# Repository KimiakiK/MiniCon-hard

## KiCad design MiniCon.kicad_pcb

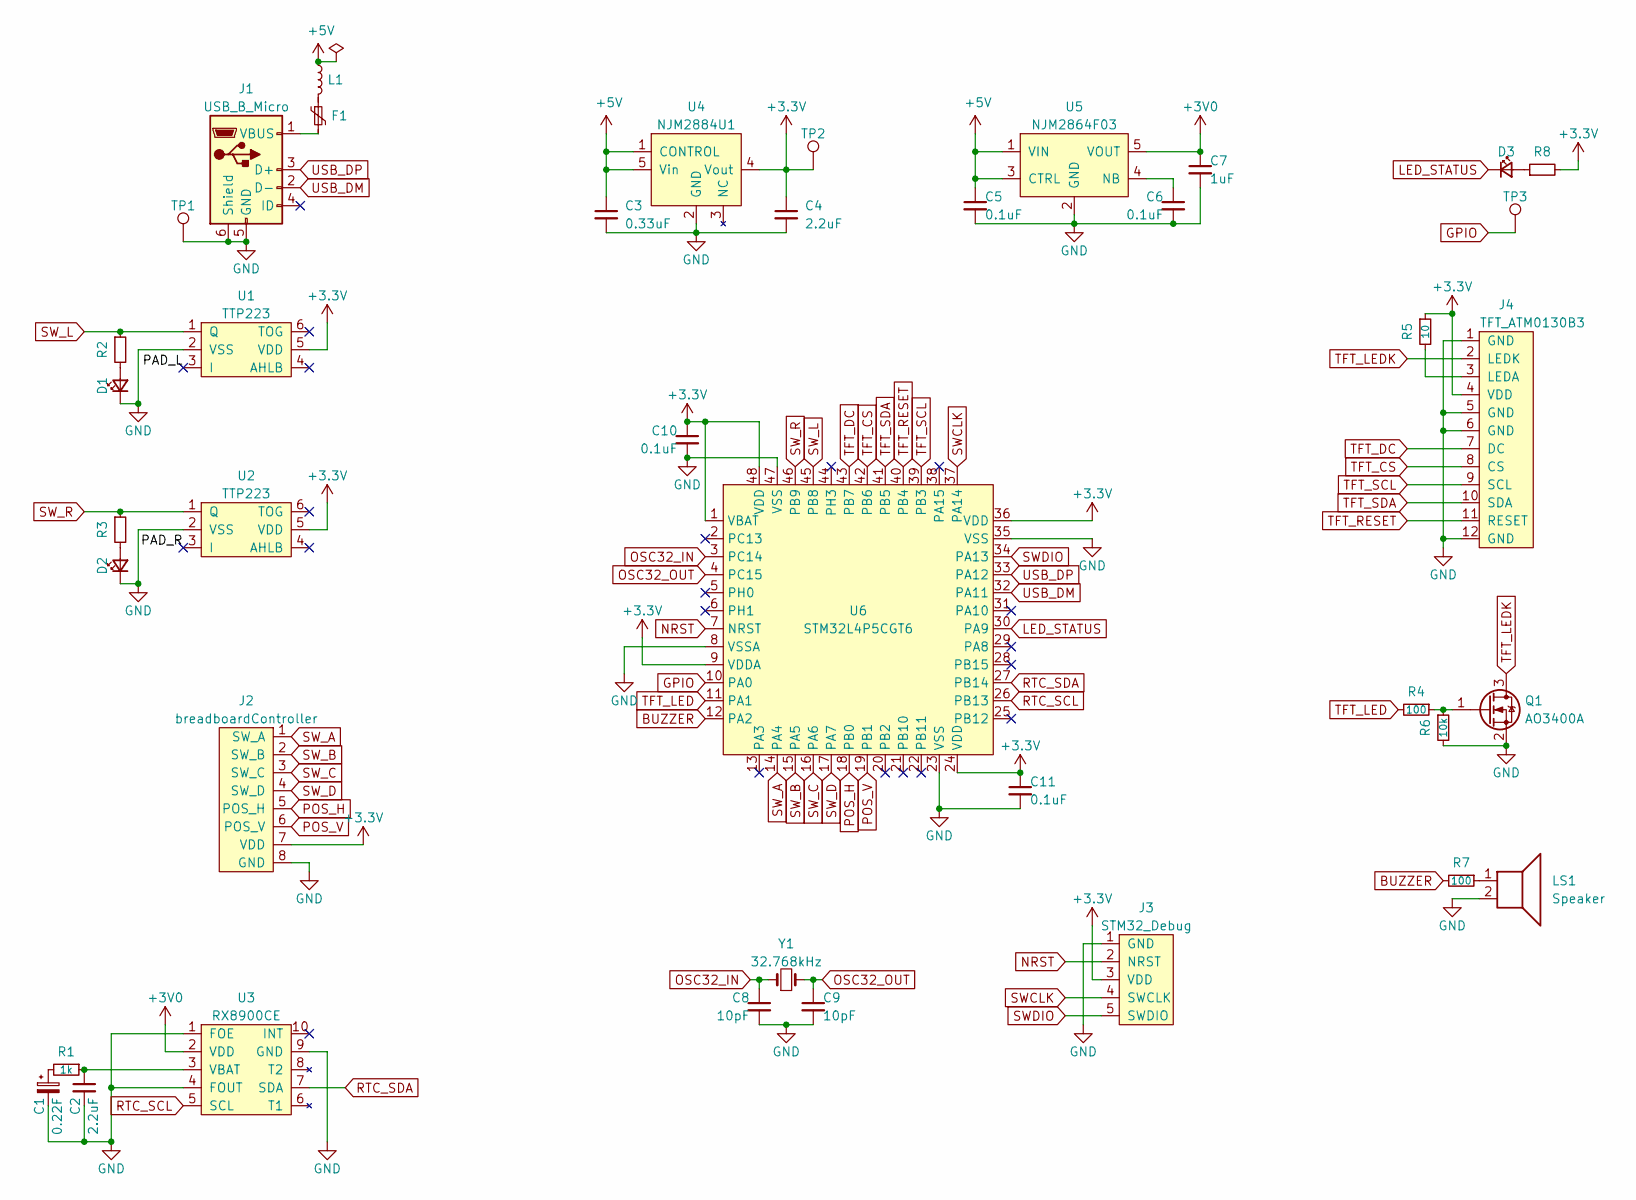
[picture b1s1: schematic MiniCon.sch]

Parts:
C1: 0.22F; DCK-3R3E224-E
C2, C4: 2.2uF; 1608Metric
C3: 0.33uF; 1608Metric
C5, C6, C10, C11: 0.1uF; 1608Metric
C7: 1uF; 1608Metric
C8, C9: 10pF; 1005Metric
D1, D2, D3: LED; 1608Metric
F1: Polyfuse; 1608Metric
J1: USB_B_Micro; ZX62-B-5PA
J2: breadboardController; PinHeader_1x08_P2.54mm_Vertical
J3: STM32_Debug; STM32_Debug_5pin
J4: TFT_ATM0130B3; Hirose_FH12-12S-0.5SH_1x12-1MP_P0.50mm_Horizontal
L1: L; 1608Metric
LS1: Speaker; PKMCS0909E4000
Q1: AO3400A; SOT-23
R1: 1k; 1608Metric
R2, R3, R8: R; 1608Metric
R4, R7: 100; 1608Metric
R5: 10; 1608Metric
R6: 10k; 1608Metric
TP1, TP2, TP3: TestPoint; TestPoint_THTPad_D1.3mm_Drill0.8mm
U1, U2: TTP223; SOT-23-6
U3: RX8900CE
U4: NJM2884U1; SOT-89-5
U5: NJM2864F03; SOT-23-5
U6: STM32L4P5CGT6; LQFP-48_7x7mm_P0.5mm_FusionPCB
Y1: 32.768kHz; Crystal_SMD_3215-2Pin

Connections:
+3V0: C7.1, U3.2 (VDD), U5.5 (VOUT)
+3V3: C4.1, C10.1, C11.1, J2.7 (VDD), J3.3 (VDD), J4.4 (VDD), R5.1, R8.2, TP2.1, U1.5 (VDD), U2.5 (VDD), U4.4 (Vout), U6.1 (VBAT), U6.9 (VDDA), U6.24 (VDD), U6.36 (VDD), U6.48 (VDD)
+5V: C3.1, C5.1, L1.1, U4.1 (CONTROL), U4.5 (Vin), U5.1 (VIN), U5.3 (CTRL)
/PAD_L: U1.3 (I)
/PAD_R: U2.3 (I)
BUZZER: R7.2, U6.12 (PA2)
GND: C1.2, C2.2, C3.2, C4.2, C5.2, C6.2, C7.2, C8.2, C9.2, C10.2, C11.2, D1.1 (K), D2.1 (K), J1.5 (GND), J1.6 (Shield), J2.8 (GND), J3.1 (GND), J4.1 (GND), J4.5 (GND), J4.6 (GND), J4.12 (GND), LS1.2, Q1.2 (S), R6.2, TP1.1, U1.2 (VSS), U2.2 (VSS), U3.1 (FOE), U3.4 (FOUT), U3.9 (GND), U4.2 (GND), U5.2 (GND), U6.8 (VSSA), U6.23 (VSS), U6.35 (VSS), U6.47 (VSS)
GPIO: TP3.1, U6.10 (PA0)
LED_STATUS: D3.1 (K), U6.30 (PA9)
NRST: J3.2 (NRST), U6.7 (NRST)
unnamed: C1.1, R1.2
unnamed: C2.1, R1.1, U3.3 (VBAT)
unnamed: C6.1, U5.4 (NB)
unnamed: D1.2 (A), R2.2
unnamed: D2.2 (A), R3.2
unnamed: D3.2 (A), R8.1
unnamed: F1.1, L1.2
unnamed: F1.2, J1.1 (VBUS)
unnamed: J4.3 (LEDA), R5.2
unnamed: LS1.1, R7.1
unnamed: Q1.1 (G), R4.1, R6.1
OSC32_IN: C8.1, U6.3 (PC14), Y1.1
OSC32_OUT: C9.1, U6.4 (PC15), Y1.2
POS_H: J2.5 (POS_H), U6.18 (PB0)
POS_V: J2.6 (POS_V), U6.19 (PB1)
RTC_SCL: U3.5 (SCL), U6.26 (PB13)
RTC_SDA: U3.7 (SDA), U6.27 (PB14)
SWCLK: J3.4 (SWCLK), U6.37 (PA14)
SWDIO: J3.5 (SWDIO), U6.34 (PA13)
SW_A: J2.1 (SW_A), U6.14 (PA4)
SW_B: J2.2 (SW_B), U6.15 (PA5)
SW_C: J2.3 (SW_C), U6.16 (PA6)
SW_D: J2.4 (SW_D), U6.17 (PA7)
SW_L: R2.1, U1.1 (Q), U6.45 (PB8)
SW_R: R3.1, U2.1 (Q), U6.46 (PB9)
TFT_CS: J4.8 (CS), U6.42 (PB6)
TFT_DC: J4.7 (DC), U6.43 (PB7)
TFT_LED: R4.2, U6.11 (PA1)
TFT_LEDK: J4.2 (LEDK), Q1.3 (D)
TFT_RESET: J4.11 (RESET), U6.40 (PB4)
TFT_SCL: J4.9 (SCL), U6.39 (PB3)
TFT_SDA: J4.10 (SDA), U6.41 (PB5)
USB_DM: J1.2 (D-), U6.32 (PA11)
USB_DP: J1.3 (D+), U6.33 (PA12)

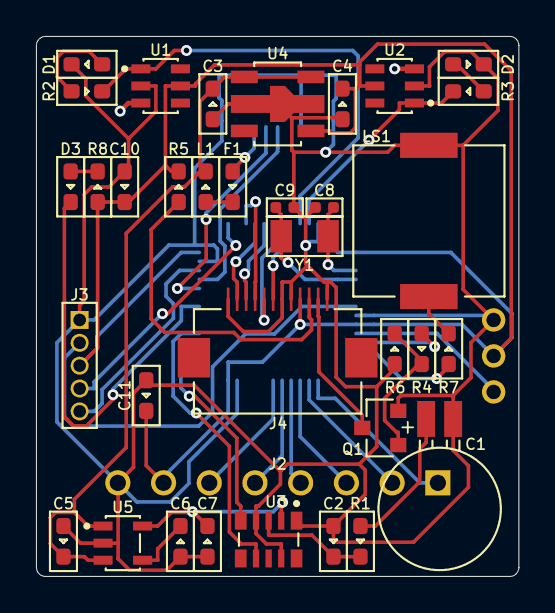
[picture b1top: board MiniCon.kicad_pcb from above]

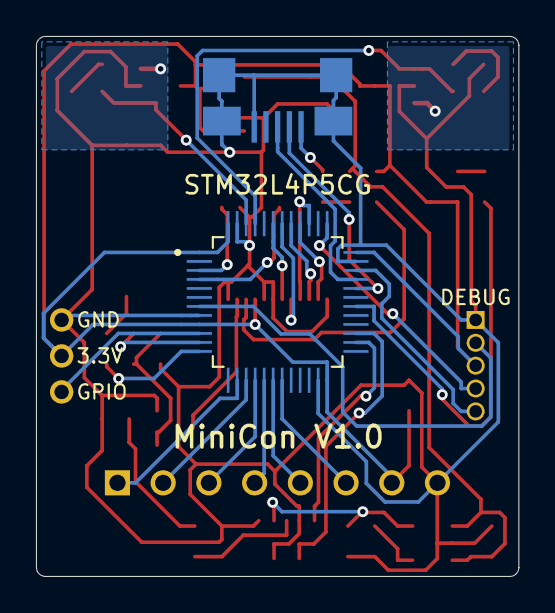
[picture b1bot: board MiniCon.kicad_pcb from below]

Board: 2 copper layers, 26.8 x 30.0 mm, 40 parts (2 on the bottom side), 42 nets.

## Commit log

2021-08-13 基板 V1.0
